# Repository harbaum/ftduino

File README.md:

# [ftDuino](http://ftduino.de): der [Arduino](http://arduino.cc) für [fischertechnik](http://fischertechnik.de)

Der ftDuino schlägt die Brücke zwischen den populären
[Arduino](http://arduino.cc)-Controllern und dem leistungsfähigen
[fischertechnik](http://fischertechnik.de)-Konstruktionsspielzeug.

Mehr Infos auf der [ftDuino-Homepage](http://ftduino.de).

The ftDuino bridges the gap between the popular [Arduino](http://arduino.cc)
controllers and the powerful [fischertechnik](http://fischertechnik.de)
construction toy.

More infos on the [ftDuino homepage](http://ftduino.de/en).

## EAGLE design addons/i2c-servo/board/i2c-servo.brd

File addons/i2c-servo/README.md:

# Mini I²C servo controller

The 30mm version featuring a single I²C port:

|  |  |
|:---:|:---:|
| [`bottom30.stl`](case/bottom30.stl) | [`top30.stl`](case/top30.stl) |

The 45mm version featuring two I²C ports:

|  |  |
|:---:|:---:|
| [`bottom45.stl`](case/bottom45.stl) | [`top45.stl`](case/top45.stl) |

# I²C-Registers

By default the adapter uses I²C address 0x11 (dec 17).

| Register | Description |
|---|---|
| 0x00/0x01 | Set servo pulse width of output 1 or 2 in 16us steps. E.g. 63 is 1ms (typical min value of a servo) and 125 is 2ms (typical max value of a servo). By default the adapter will not allow values < 53 and values > 125 to protect the servo. Example set PWM1 to 1.5ms: 0x11 0x00 0x5e |
| 0x02/0x03 | Set lower limit for servo 1 or servo 2 in 16us steps. Default value is 63. Values written to registers  0x00/0x01 lower than the limits specified here are mapped to this limit. |
| 0x04/0x05 | Set upper limit for servo 1 or servo 2 in 16us steps. Default value is 125. Values written to registers  0x00/0x01 higher than the limits specified here are mapped to this limit. |
| 0x06/0x07 | Set offset for servo 1 or servo 2. Default value is 0. The offset is added to the PWM value written to registers 0 or 1 _after_ the limit takes place. This is useful to adjust the center position of a servo. |
| 0x08 | Set I²C address. The new address can be any address >= 0x03 and <= 0x77 except 0x3c (which is reserved because the OLED uses it). |
| 0x09 | Writing 0xa5 to this register stores the values from registers 0x02 to 0x08 in eeprom. These settings will then become permanent over power loss and reboot. |
| Read 0x00 | Reading register 0x00 returns the formware version in BCD, e.g. 0x10 for version 1.0 |
| Read 0x01+ | Reading any other register returns 0x5a |

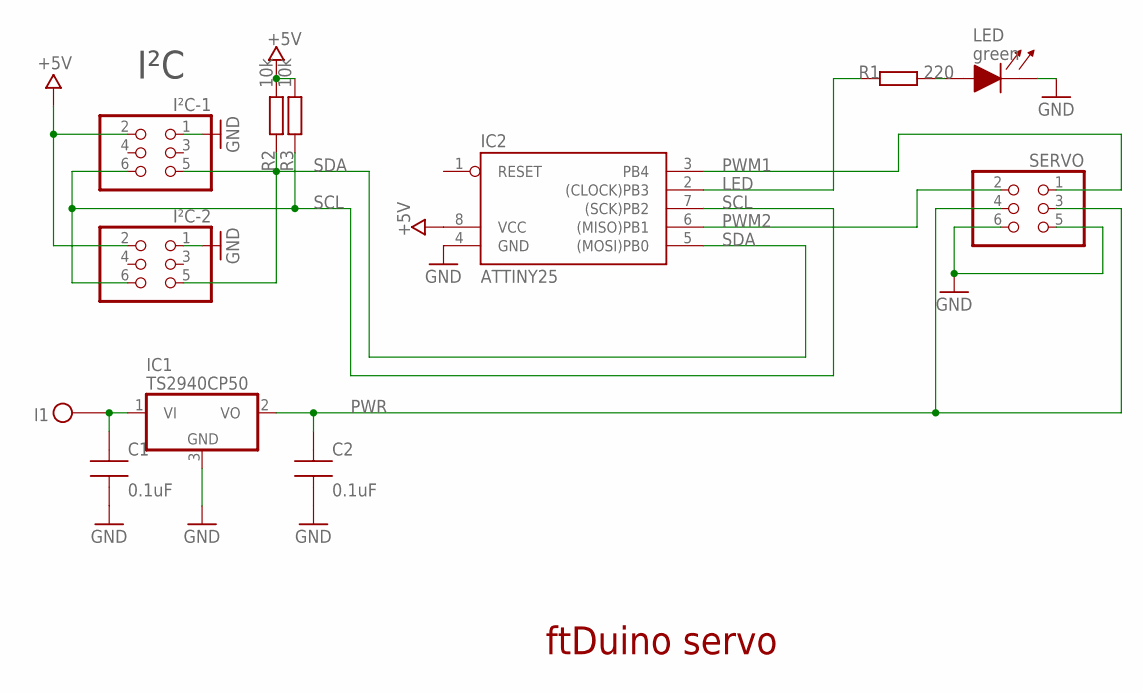
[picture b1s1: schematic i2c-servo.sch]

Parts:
C1, C2: 0.1uF; CAP0805-NP
H5: I1; FT-HUELSE
IC1: TS2940CP50; TO252
IC2: ATTINY25; SOIC8
I²C-1, I²C-2: PINHD-2X3_2.54-SMD; 2X03SMD
LED: green; LED0805
R1: 220; M0805
R2, R3: 10k; M0805
SERVO: PINHD-2X3_2.54-SMD; 2X03SMD

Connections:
+5V: IC2.8 (VCC), I²C-1.2, I²C-2.2, R2.2, R3.2
GND: C1.2, C2.2, IC1.3 (GND), IC2.4 (GND), I²C-1.1, I²C-2.1, LED.1 (CA), SERVO.5, SERVO.6
LED: IC2.2 ((CLOCK)PB3), R1.1
unnamed: C1.1, H5.D1, IC1.1 (VI)
unnamed: LED.2 (AN), R1.2
PWM1: IC2.3 (PB4), SERVO.1
PWM2: IC2.6 ((MISO)PB1), SERVO.2
PWR: C2.1, IC1.2 (VO), SERVO.3, SERVO.4
SCL: IC2.7 ((SCK)PB2), I²C-1.6, I²C-2.6, R3.1
SDA: IC2.5 ((MOSI)PB0), I²C-1.5, I²C-2.5, R2.1

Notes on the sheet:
I²C
ftDuino servo

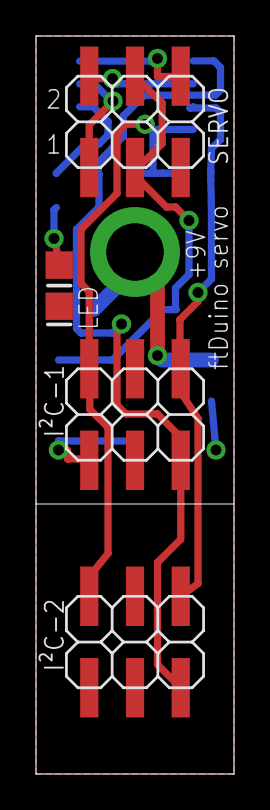
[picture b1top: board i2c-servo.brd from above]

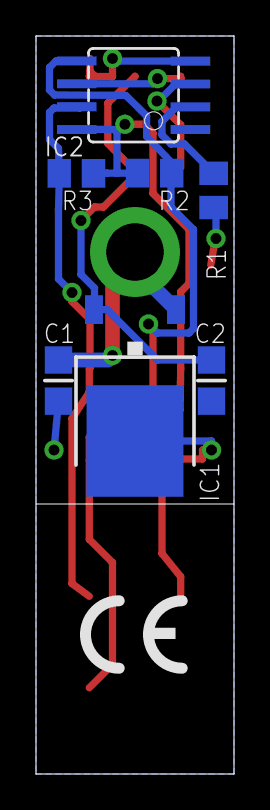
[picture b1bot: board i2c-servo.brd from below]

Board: 2 copper layers, 11.0 x 41.0 mm, 12 parts (7 on the bottom side), 10 nets.

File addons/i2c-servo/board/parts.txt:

Part name                Description            Digikey No
------------------------------------------------------------------
IC1                      TS2940CP50             TS2940CP50ROG-ND      
IC2                      Attiny25 SOIC8         ATTINY25-20SSU-ND 
R1                       220 0805               CR0805-JW-221ELFTR-ND, any < 5% 0805 220R resistor
R2,R3                    10k 0805               311-10KARTR-ND, any < 5% 0805 10k resistor
C1,C2                    100nF 0805             399-7367-2-ND, any ceramic 100nF >=10V 0805 will do
LED                      green 0805             475-1410-2-ND, any cheap 0805 led will do
I²C1, I²C2, SERVO        6 pin 2.54mm SMD pin   54202-S0803LF-ND or similar regular 2.54mm 6 pin smd 
I1                       metal sleeve           fischertechnik sleeve as on ftDuino itself

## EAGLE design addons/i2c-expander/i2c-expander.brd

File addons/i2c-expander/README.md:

# I²C expander

|  |  |
|:---:|:---:|
| [`bottom.stl`](bottom.stl) | [`top.stl`](top.stl) |

The I²C expander expands the single 5V I²C port of a ftDuino or
fischertechnik TX controller by three more ports and contains a level
shifter to bridge to a fischertechnik TXT compatible 3.3V port.

This adapter can e.g. be used to connect the ```fischertechnik 
Kombisensor 158402 3-in-1 Orientierungssensor``` ([PDF](https://content.ugfischer.com/cbfiles/fischer/Zulassungen/ft/158402-Kombisensor-Kurzanleitung-BMX055-2017-06-09.pdf)) which is meant to be connected to the TXT and its 3.3V
I²C:

This is how the setup looks right before assembly:

## Parts

All parts are available from e.g. [Reichelt](http://www.reichelt.de).

You need:

  - 1x 10 pin header [WSL 10G](https://www.reichelt.de/Pfosten-Wannenstecker/WSL-10G/3/index.html?ACTION=3&GROUPID=7437&ARTICLE=22816&SEARCH=wannenstecker&START=0&OFFSET=16&)
  - 4x 6 pin header [WSL 6G](https://www.reichelt.de/Pfosten-Wannenstecker/WSL-6G/3/index.html?ACTION=3&GROUPID=7437&ARTICLE=85732&SEARCH=wannenstecker&START=0&OFFSET=16&)
  - 2x resistors [22k ohms SMD](https://www.reichelt.de/SMD-0805-von-1-bis-910-kOhm/SMD-0805-22-0K/3/index.html?ACTION=3&GROUPID=7971&ARTICLE=32902&SEARCH=0805%2B22%252C0k&START=0&OFFSET=16&)
  - 2x N channel MOSFET [BSS 123](https://www.reichelt.de/BS-Transistoren/BSS-123-SMD/3/index.html?ACTION=3&GROUPID=2884&ARTICLE=41435&SEARCH=BSS123&START=0&OFFSET=16&)
  - 1x power regulator [TPS 77033 DBVT](https://www.reichelt.de/ICs-TLC-TSA-/TPS-77033-DBVT/3/index.html?ACTION=3&GROUPID=5480&ARTICLE=188754&SEARCH=77033&START=0&OFFSET=16&)

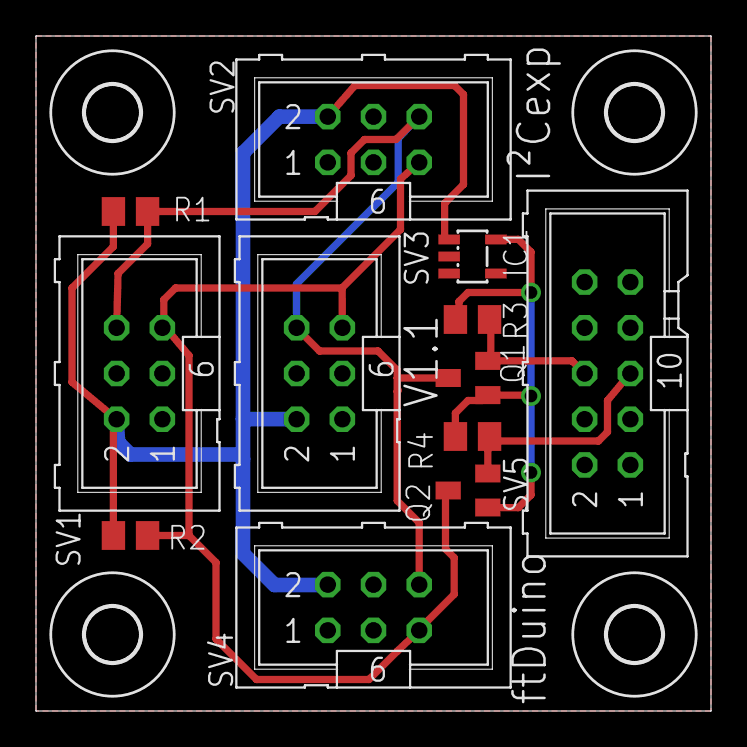
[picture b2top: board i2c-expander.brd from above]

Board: 2 copper layers, 37.5 x 37.5 mm, 16 parts (0 on the bottom side), 7 nets.

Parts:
H1, H2, H3, H4: MOUNT-HOLE3.0; 3,0
IC1: TLV77033; SOT23-DBV
Q1, Q2: BSS123; SOT23
R1, R2, R3, R4: 22k; M0805
SV1, SV2, SV3, SV4: ML6
SV5: ML10

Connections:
GND: IC1.2, IC1.3, SV1.1, SV2.1, SV3.1, SV4.1, SV5.1
unnamed: Q1.2, R3.1, SV5.6
unnamed: Q2.2, R4.1, SV5.5
unnamed: IC1.5, Q1.1, Q2.1, R3.2, R4.2
SCL_5: Q1.3, R1.1, SV1.6, SV2.6, SV3.6, SV4.6
SDA_5: Q2.3, R2.1, SV1.5, SV2.5, SV3.5, SV4.5
VCC: IC1.1, R1.2, R2.2, SV1.2, SV2.2, SV3.2, SV4.2

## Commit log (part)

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2018-04-06 Added ultrasonic example
2018-04-09 Extended i2c slave
2018-04-25 Added plug description
2018-04-25 Inner measurement
2018-04-27 MIDIUSB install
2018-04-27 Hardware pwm music example
2018-04-27 Example for hardware generated tones
2018-04-27 Kleine Optimierungen
2018-05-06 I2C master with multiple clients example
2018-05-08 Multi i2c setup
2018-05-11 Added thermosensor section
2018-05-11 Temperature example
2018-05-15 Updated manual
2018-05-16 Stepper motor example
2018-05-17 Cleanup stepper motor example
2018-05-17 Stepper motor chapter
2018-05-17 Irq driven stepper example
2018-05-21 Add setpper motor server
2018-05-23 Fixed ultrasonic bit rate calculation
2018-05-24 Rules required for WebUSB
2018-05-24 WebUSB web pages
2018-05-24 WebUSB console demo
2018-05-24 USB 2.1 config for WebUSB
2018-05-24 Add WebUSB library
2018-05-24 Release with WebUSB and Ultrasonic fix
2018-05-24 Make WebUSB example depend on USB 2.1
2018-05-24 LED buttons
2018-05-25 Some WebUSB explanations
2018-05-28 Order email
2018-05-29 Increase ultrasonic baudrate precision
2018-06-05 Simple servo demo
2018-06-06 Servo example
2018-06-06 Fix some typos
2018-06-06 Servo wiring update
2018-06-06 Updated servo photo
2018-06-08 Further work on the servo connection
2018-06-13 Relaase incl servo example
2018-06-18 Programming introduction
2018-06-24 Added section for the ft-extender
2018-06-25 Add photo of ftExtender
2018-07-02 Android demo app with matching ftDuino sketch
2018-07-02 Added readme
2018-07-04 Andoid-App description
2018-07-04 Case for i2c level shifter
2018-07-23 Added ultrasonic demo
2018-07-25 Fix images
2018-07-25 Direct links to STL files
2018-07-25 Spell checking
2018-07-30 PDF download changed
2018-07-30 Extended readme
2018-07-31 Added some web page
2018-08-03 WWW cleanup
2018-08-03 WWW update
2018-08-04 Update image
2018-08-05 One more image
2018-08-06 Scale image
2018-08-12 Added some links
2018-08-12 Pimped webusb landing page
2018-08-12 Changed highlighting
2018-08-14 english webusb page
2018-08-19 Shop link etc
2018-08-21 Added bickly-lite/webusb demo
2018-08-21 Added missing screenshots
2018-08-22 Brickly in manual
2018-08-22 Spelling
2018-08-22 Fix page numbering
2018-08-23 Added section about umweltsensor
2018-08-29 Added schematic and board
2018-08-31 Redirect to issues page
2018-08-31 Added quickstart instructions
2018-09-19 Redirect to ftduino.de
2018-09-19 Mobile robot image
2018-09-20 Added remark about line endings
2018-09-21 Added Mac screenshot and IoTest
2018-09-21 Fix URL typo
2018-09-21 Fix english url
2018-09-23 Fix email address
2018-09-25 New examples incl. S4A
2018-09-25 S4A description
2018-09-25 S4A example
2018-09-28 Motor support for S4A
2018-10-18 Release 0.0.11 incl examples for internal OLED
2018-10-18 Chapter explaining the OLED-ftDuino
2018-10-19 S4A ftDuino sprite
2018-10-19 Add platformio library.json manifest files
    This allows to register the library at the platfomio library registry.
    Documentation: http://docs.platformio.org/en/latest/librarymanager/config.html
2018-11-08 Fix I2cSlave
2018-11-11 New chapter about low memory situations
2018-11-12 Manual section about ftduino usage in schools
2018-11-25 Add impressum
2018-11-26 Trigger build
2018-12-05 New links
2018-12-05 Fix formatting
2018-12-18 Update web links
2018-12-18 Minecraft mod test release
2018-12-18 Minecraft mod link
2018-12-19 Updated release for ftPedia 4_18
2018-12-19 Updated release for ftPedia 4_18 ... 2nd try
2018-12-19 Fix json parser
2018-12-20 update to ftduino_direct v1.2 -> I2C pwm/servo shield support Signed-off-by: PeterDHabermehl <peter.habermehl@gmx.de>
2018-12-20 Update to ftduino_direct v1.2.1 - added "pwm_halt" command to shut off all pwm ports at once. Signed-off-by: PeterDHabermehl <peter.habermehl@gmx.de>
2018-12-22 Input support for Minecraft
2018-12-26 Minecraft mod v0.0.3
2018-12-26 Minecraft documentation
2018-12-28 Simplified github urls
2018-12-29 More links simplification
2018-12-29 Updated shop links
2018-12-29 Fix typo
2018-12-30 Added news sectioon
2018-12-30 Fix typos
2018-12-30 Update buy section
2018-12-31 Rename ftduino_direct.1.2.1.ino.hex to ftduino_direct_1_2_1.ino.hex
2019-01-10 Fix links
2019-01-11 Updated ftduino_direct binary to v1.3.2 Signed-off-by: PeterDHabermehl <peter.habermehl@gmx.de>
2019-01-14 Power supply suggestions and warnings
2019-01-16 HTML version of the manual
2019-01-17 Power supply links
2019-01-17 Fix html
2019-01-18 Minecraft blocks emit smoke if ftduino is not connected
2019-01-25 Add Senso/Simon Says game
2019-02-05 Added plotter
2019-02-07 Plotter section in manual
2019-02-08 Slightly increased bootloader timeout
2019-02-20 Servo controller cases
2019-02-21 MiniServoAdapter example
2019-02-21 Added mini servo adapter to manual
2019-02-21 Add new images
2019-02-21 Fix html header
2019-02-21 Add missing image
2019-02-21 Fix verbatim rendering in html
2019-02-24 Fix chapter numbering
2019-03-04 Link to ft catalogue
2019-03-04 Fix catalog link
2019-03-15 Improve RX buffer handling
2019-03-15 Scratch3 test release
2019-03-18 Update scratch3 demo
2019-03-18 Release WebUSB handling
2019-03-18 Link to scratch3
2019-03-18 Demo screenshot
2019-03-18 Fix exception when no ftDuino is connected
2019-03-18 Preserve start and stop button listeners
2019-03-19 Update manual for scratch3
2019-03-19 Links to pi geek magazine
2019-03-20 Update scratch
2019-03-20 Remove binary apk from repository
2019-03-20 Adjust www links to point to apk in release
2019-03-21 Removed unused map files
2019-03-21 Scratch 30 offline usage
2019-03-29 Scratch 3 synchronous io
2019-03-31 plotter option mini servo controller
2019-04-01 Update scratch 3
2019-04-02 Release 0.0.14
2019-04-02 Use github release for 0.0.13 and up
2019-04-02 Fix 0.0.13 link
2019-04-02 Remove packages now served from git releases
2019-04-02 Lidar demo for OLED ftDuino
2019-04-04 Scratch3 inout hat
2019-04-09 Tool to change mini servo adapter address
2019-04-09 Updated mini servo chapter
2019-04-09 Link to servo adapter
2019-04-09 Fix image size
2019-04-12 Update scratch 3.0 and async ftduino input
2019-04-29 Some more Modemmanager troubleshooting
2019-05-02 Update scratch3
2019-05-03 Cleaned up scratch3 solution
2019-05-07 Windows 8.1 installation instructions
2019-05-29 Manual fixed and OLED lib update
2019-06-17 Fix underscores encoding in manual
2019-07-28 Explanations regarding the Ubuntu store
2019-09-11 Mini-Servo-Adapter schematic, pcb and firmware
2019-09-16 Add vendor
2019-09-17 Add shop link
2019-10-01 Link to google translated manual
2019-10-02 Hide some google translate stuff
2019-10-17 Scratch3 update
2019-10-17 Update www
2019-10-17 Fix #6
2019-10-17 MacOS 10.15 Catalina workaround
2019-10-18 HTML cleanups
2019-10-18 More html cleanups
2019-10-18 Attempt to fix scratch3 hat
2019-10-18 prepare release 0.0.15
2019-10-21 Minor html table cleanup
2019-10-25 Fix html tables
2019-10-31 Index should start at zero
    See https://github.com/arduino/arduino-cli/issues/456
2019-11-06 Define tmp file to make it work with arduino-cli
    Arduino-cli expects the value `recipe.output.tmp_file` to be set.
2020-03-05 Added Eggbot
2020-03-14 Added rfid demo
2020-03-15 Control ft lamps with RFID
2020-03-15 Added mfrc522 rfid example
2020-04-18 Removed scratch input HAT
2020-04-18 Add missing svg
2020-04-18 Attempt to clean up scratch mess ...
2020-07-05 Link to ft-HAT
2020-07-06 Add RPi-Mag sighting
2020-07-07 Link to book
2020-07-09 Bluetooth examples
2020-07-09 Adjust book links
2020-07-10 Add Ftduino M1 control to ArduinoBlue example
2020-07-12 Add bluetooth instructions
2020-07-12 Resize images
2020-07-12 Fix manual
2020-07-13 Link to html instead of pdf
2020-07-13 Update ArduinoBlue examples
2020-07-13 Release 0.0.16
2020-07-14 Use span instead of font element
2020-07-14 Hide some decorations
2020-07-14 Update translation handling
2020-07-14 Hide some google elemets
2020-07-17 Minor bridge cleanup
2020-08-29 ftDuinoBlue landing page
2020-08-29 More descriptions
2020-09-03 Add picnic css
2020-09-15 Add i2c servo board design
2020-09-15 Add ftDuinoBlue demo sketch
2020-09-15 Added ArduinoBlue
2020-09-18 Some more ftduinoblue demos
2020-09-18 Fix xml display
2020-09-18 Update ftduinoblue for uno and hm10
2020-09-18 fix closing tag
2020-09-19 Limit page width
2020-09-19 Fix utf8 encoding
2020-09-19 Add serial1 support for ftduino
2020-09-21 ftduinoblue refactoring
2020-09-21 Update apl
2020-09-21 Adjust name
2020-09-22 Nav menu
2020-09-22 Increase font size
2020-09-24 Some more explanations
2020-09-28 Add placement description
2020-09-28 Demo 2 explanations
2020-09-28 Fix demo2 text
2020-09-29 Link to app store
2020-09-29 More explanations
2020-09-29 ftduinoblue sketch moved into own repository
2020-10-12 Add schematic for uno setup
2020-10-12 Fix layout
2020-10-12 More fixes
2020-10-12 Create readme.md
    Just a hint to use the ...45 case parts for the commercially available boards.
2020-10-20 Updates bluetooth demos
2020-10-20 Fix CJMCU-750 links
2020-10-23 Added MINTronics link
2020-10-23 Added MINTronics link
2020-10-29 Fix example links
2020-12-11 Add examples for ftDuino bluetooth adapter
2020-12-11 Fix release number to 0.0.17
2020-12-11 Adjust release file location
2020-12-16 New bluetooth module
2020-12-16 Fix link
2020-12-16 ftDuino robot image
2020-12-16 remove border
2020-12-31 Add MINTronics links
2021-01-01 Addons link
2021-01-04 Added video link
2021-01-06 Fix various typos
2021-01-06 Some more ftDuino info
2021-01-06 Fix image
2021-01-06 Fix brace
2021-01-06 Fix double image
2021-01-06 Another fix
2021-01-08 Fix references
2021-01-10 Make ultrasonic and WebUSB configurable. Prepare new output driver
2021-01-12 Update installation chapter
2021-01-12 Adjust caption
2021-01-14 Automatic output option
2021-01-17 First ftDuinoSimple support for TLE94108EL
2021-01-17 Output driver auto detection
2021-01-27 Add ec sketch
2021-01-27 Report bytes received
2021-01-27 Add blockly junior demo
2021-01-27 Use Textencoder
2021-01-28 Adjust EC timing
2021-01-28 Fix ec stop logic
2021-01-28 Make EC control a two wheel robot
2021-01-28 Relax timing
2021-01-28 Another bug fix in ec
2021-01-28 Implement tx queue
2021-02-04 Option for drv8908 output driver
2021-05-08 Add support for FT controllers
2022-03-23 :fire: Styled Impressum and determine page to redirect to based on the browser locale
2022-03-23 :flag_gb: English Site
2022-03-23 CSS Fixes
2022-03-23 DE Page
2022-03-23 use correct link
2022-04-06 Update ftduinoblue doc
2022-04-11 Attempt to add ft robby support
2022-07-05 Fix robby command
2022-07-06 Gracefully handle disconnects
2022-07-06 Fix connect exception handling
2022-07-06 Fix button handling on touch devices
2022-07-07 Explain filter problem
2022-07-08 Fix blueotooth request
2022-07-08 Try to adopt to chromium bug
2022-07-08 Undo accidentially undoing the fix
2022-09-16 Add libraries.properties files for IDE 2.0
2022-09-16 Complain if yet unsupported output drivers are selected
2022-09-16 Verify webusb settings
2022-09-16 More WebUSB sanitiy checks
2022-09-16 Even more WebUSB sanity checks
2022-09-16 Release 0.0.18
2022-09-20 Fix library.properties for IDE 1.x
2022-09-20 Update 0.0.18 releaase
2022-09-20 Fix image border
2022-09-23 Fix package index
2022-10-07 Add output driver chip detect sketch
2022-10-11 Add library support for TLE94108
2022-10-12 Finalize drv8908 detection and usage
2022-10-12 Full driver support for FtduinoSimple
2022-10-12 Fix drv8908 duty cycle mapping
2022-10-14 Remove some dependencies and fix a little visibility issue
2022-10-21 Increase SPI speed to 4Mhz with DRV8908
2022-10-21 Adjust ChipDetect blink timng
2023-03-04 Fix typos in manual
2023-03-04 Fix typos in Ftduino code
2023-04-24 Link to ftDuino32
2023-10-31 Add 0.0.19
2023-10-31 Add missing DRV8908 defines
2023-10-31 Update package index
2024-02-06 Remove shop link on request by Gundermann
2024-02-06 Update index.html and added Gundermann link again
2024-02-06 Update index.html and added Gundermann again
2024-02-06 Update index.html Gundermann added again
2024-02-06 Update index.html Gundermann added
2024-02-06 Update index.html typo fixed
2026-03-12 Attempt to fix avrdude.conf issue
